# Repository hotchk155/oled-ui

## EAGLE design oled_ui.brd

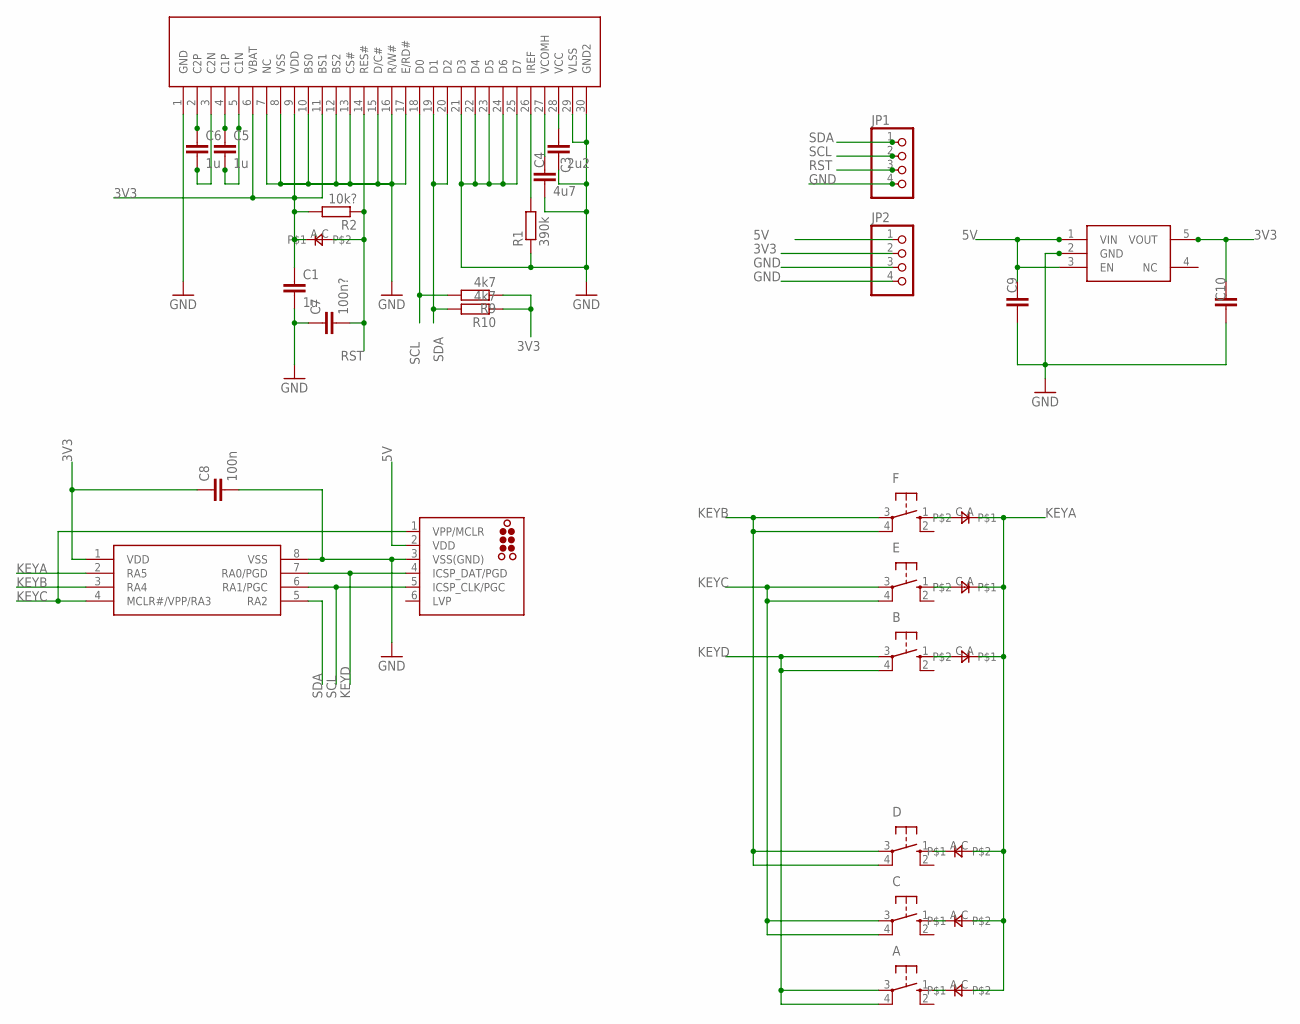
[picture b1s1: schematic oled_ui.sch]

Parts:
A: 10-XX; B3F-10XX
B: 10-XX; B3F-10XX
C: 10-XX; B3F-10XX
C1, C5, C6: 1u; C0805
C3: 2u2; C0805
C4: 4u7; C0805
C7: 100n?; C0805
C8: 100n; C0805
C9, C10: C-EUC0805; C0805
D: 10-XX; B3F-10XX
D1: 0805DIODE
E: 10-XX; B3F-10XX
F: 10-XX; B3F-10XX
IC1: PIC12F1822SO08; SO08
IC2: MIC5504-2.8YM5-TR; SOT23-5
ICSP: TC2030-MCP-NL
JP1, JP2: PINHD-1X4; 1X04
R1: 390k; R0805
R2: 10k?; R0805
R9, R10: 4k7; R0805
U$1: OLED_MODULE; OLED_CONN
U$3, U$4, U$5, U$6, U$7, U$8: 0805DIODE

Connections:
3V3: C1.1, C8.1, C10.1, D1.A, IC1.1 (VDD), IC2.5 (VOUT), JP2.2, R2.2, R9.1, R10.1, U$1.6 (VBAT), U$1.9 (VDD), U$1.11 (BS1)
5V: C9.1, IC2.1 (VIN), IC2.3 (EN), ICSP.2 (VDD), JP2.1
GND: C1.2, C3.2, C4.2, C7.1, C8.2, C9.2, C10.2, IC1.8 (VSS), IC2.2 (GND), ICSP.3 (VSS(GND)), JP1.4, JP2.3, JP2.4, R1.1, U$1.1 (GND), U$1.7 (NC), U$1.8 (VSS), U$1.10 (BS0), U$1.12 (BS2), U$1.13 (CS#), U$1.15 (D/C#), U$1.16 (R/W#), U$1.17 (E/RD#), U$1.21 (D3), U$1.22 (D4), U$1.23 (D5), U$1.24 (D6), U$1.25 (D7), U$1.29 (VLSS), U$1.30 (GND2)
KEYA: IC1.2 (RA5), U$3.A, U$4.A, U$5.A, U$6.C, U$7.C, U$8.C
KEYB: D.3, D.4 (P1), F.3, F.4 (P1), IC1.3 (RA4)
KEYC: C.3, C.4 (P1), E.3, E.4 (P1), IC1.4 (MCLR#/VPP/RA3), ICSP.1 (VPP/MCLR)
KEYD: A.3, A.4 (P1), B.3, B.4 (P1), IC1.7 (RA0/PGD), ICSP.4 (ICSP_DAT/PGD)
unnamed: C6.2, U$1.3 (C2N)
unnamed: C6.1, U$1.2 (C2P)
unnamed: C5.1, U$1.4 (C1P)
unnamed: C5.2, U$1.5 (C1N)
unnamed: F.1 (S), U$3.C
unnamed: C3.1, U$1.28 (VCC)
unnamed: D.1 (S), U$6.A
unnamed: C4.1, U$1.27 (VCOMH)
unnamed: C.1 (S), U$7.A
unnamed: R1.2, U$1.26 (IREF)
unnamed: E.1 (S), U$4.C
unnamed: B.1 (S), U$5.C
unnamed: A.1 (S), U$8.A
RST: C7.2, D1.C, JP1.3, R2.1, U$1.14 (RES#)
SCL: IC1.6 (RA1/PGC), ICSP.5 (ICSP_CLK/PGC), JP1.2, R9.2, U$1.18 (D0)
SDA: IC1.5 (RA2), JP1.1, R10.2, U$1.19 (D1), U$1.20 (D2)

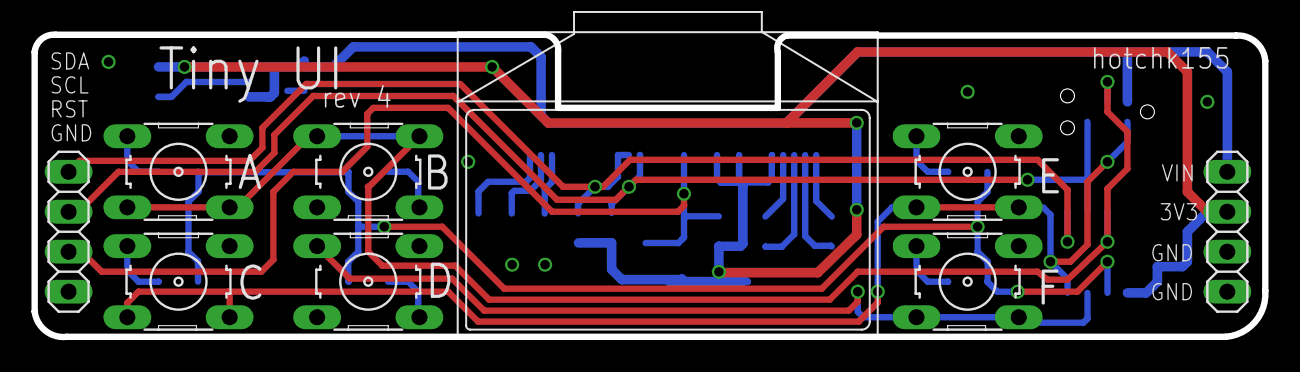
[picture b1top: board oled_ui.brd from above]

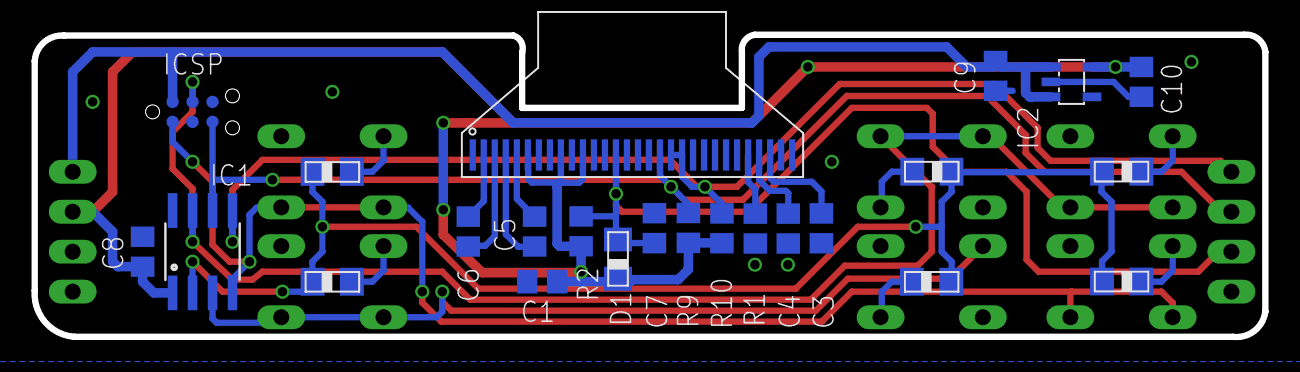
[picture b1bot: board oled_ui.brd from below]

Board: 2 copper layers, 78.2 x 19.2 mm, 32 parts (23 on the bottom side), 23 nets.

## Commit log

2015-11-15 :lollipop: Added .gitattributes & .gitignore files
2015-11-21 OOPS!
2015-11-21 tweak
2015-11-21 stuff
2015-11-25 big flip
2015-11-26 pcb rev 2
2015-12-21 updates in progress
2015-12-26 Revert "updates in progress"
    This reverts commit 001d56b77ca17e324d01e8b0934cb9d53080aba6.
2016-01-13 work in progress
2016-03-05 ready?
2016-03-05 PCB V3
2016-12-04 pcb rev 4

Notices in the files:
parts and their libraries:
tag-connect: ©2009 ROFA.cz - modified and updated by Robert Darlington ‹rdarlington@gmail.com›
